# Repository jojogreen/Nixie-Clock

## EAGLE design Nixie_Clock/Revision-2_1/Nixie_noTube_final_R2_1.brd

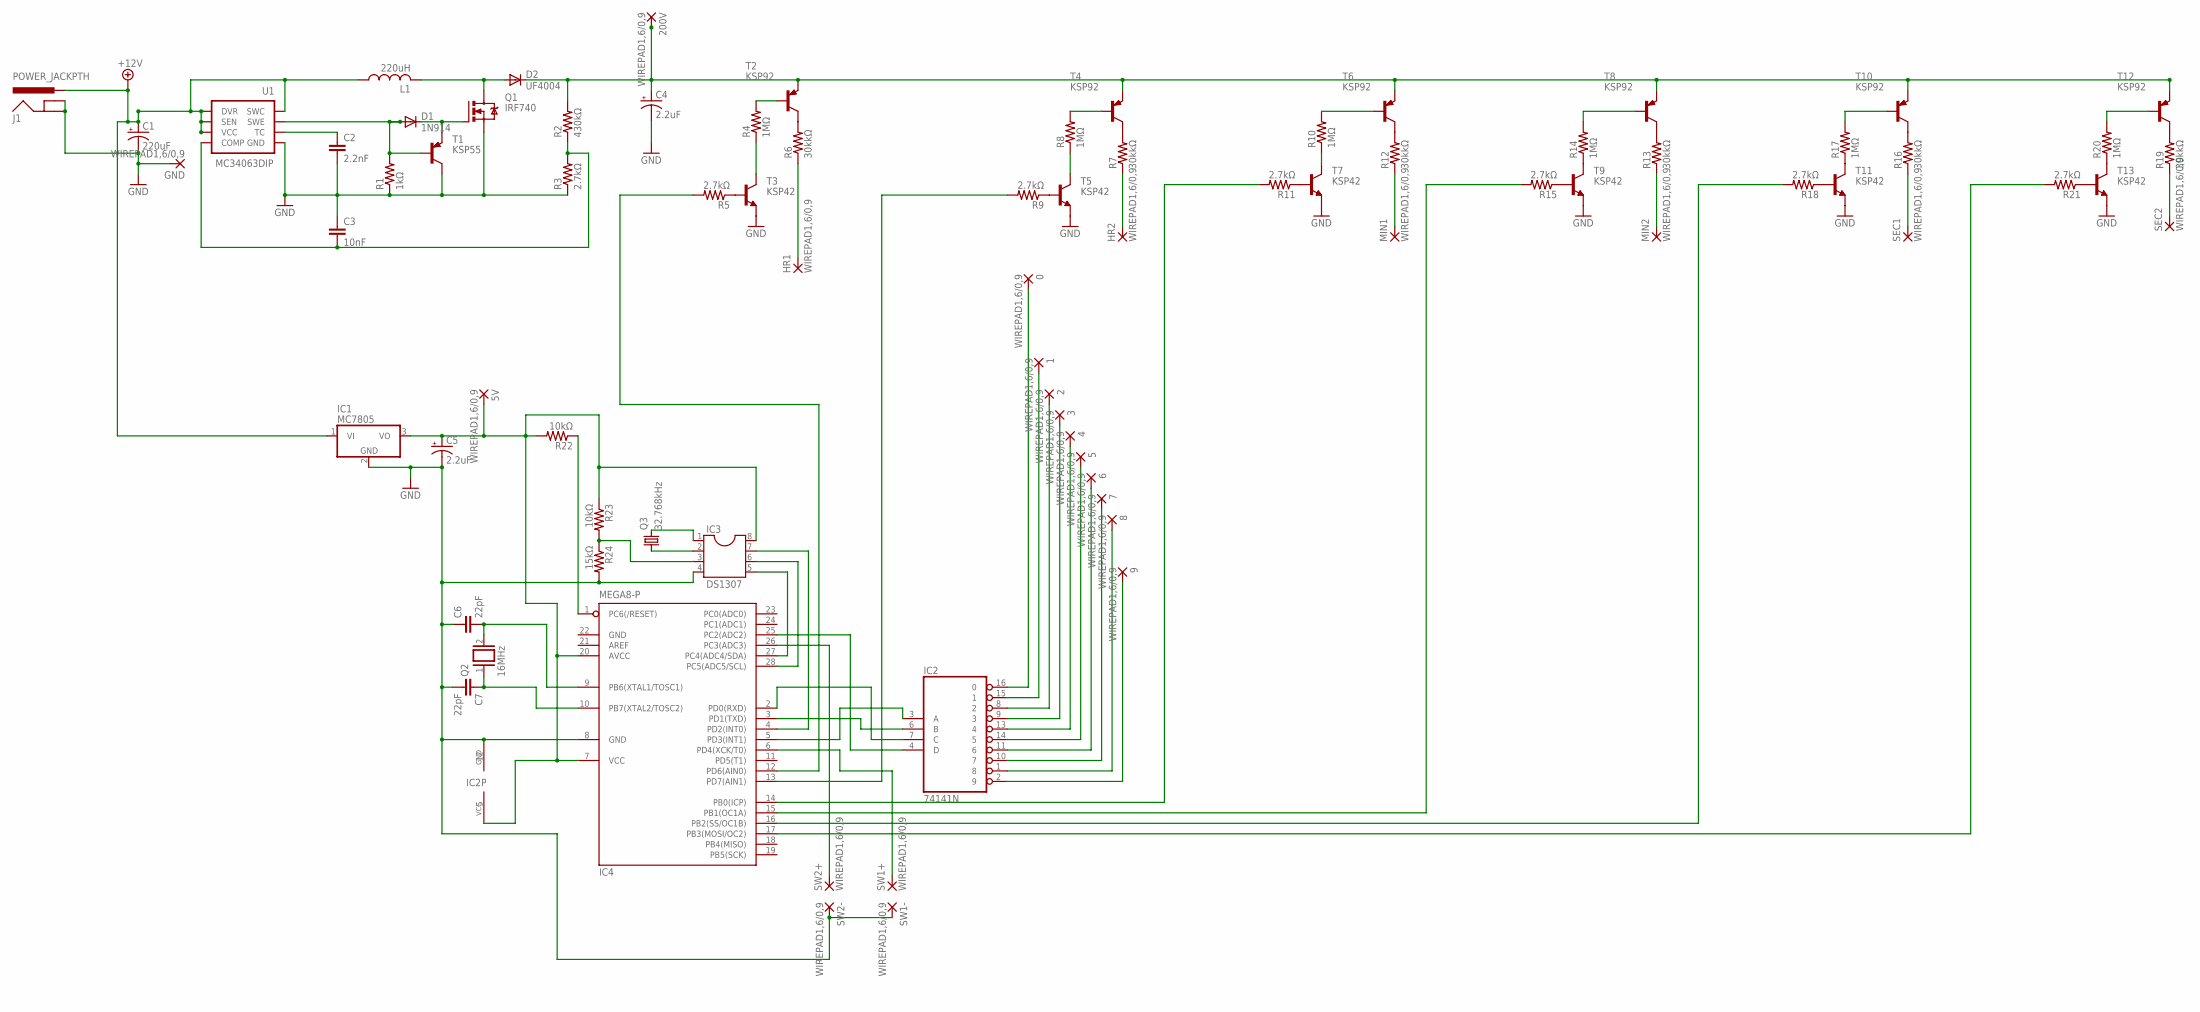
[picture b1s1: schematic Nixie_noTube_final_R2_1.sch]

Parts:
0, 1, 2, 3, 4, 5, 5V, 6, 7, 8, 9, 200V: WIREPAD1,6/0,9; 1,6/0,9
C1: 220uF; E5-10,5
C2: 2.2nF; CAP-PTH-SMALLEZ
C3: 10nF; CAP-PTH-SMALLEZ
C4, C5: 2.2uF; CPOL-RADIAL-100UF-25V
C6, C7: 22pF; C2.5-3
D1: 1N914; DO41-10
D2: UF4004; DO41-10
GND: WIREPAD1,6/0,9; 1,6/0,9
HR1, HR2: WIREPAD1,6/0,9; 1,6/0,9
IC1: MC7805; TO220V
IC2: 74141N; DIL16
IC3: DS1307; DIL08
IC4: MEGA8-P; DIL28-3
J1: POWER_JACKPTH; POWER_JACK_PTH
L1: 220uH; 6000-XXXX-RC
MIN1, MIN2: WIREPAD1,6/0,9; 1,6/0,9
Q1: IRF740; TO220BV
Q2: 16MHz; QS
Q3: 32.768kHz; TC26H
R1: 1kΩ; 0204/7
R2: 430kΩ; 0204/7
R3, R5, R9, R11, R15, R18, R21: 2.7kΩ; 0204/7
R4, R8, R10, R14, R17, R20: 1MΩ; 0204/7
R6, R7, R12, R13, R16, R19: 30kkΩ; 0204/7
R22, R23: 10kΩ; 0204/7
R24: 15kΩ; 0204/7
SEC1, SEC2: WIREPAD1,6/0,9; 1,6/0,9
SW1+, SW1-, SW2+, SW2-: WIREPAD1,6/0,9; 1,6/0,9
T1: KSP55; TO92-EBC
T2, T4, T6, T8, T10, T12: KSP92; TO92-EBC
T3, T5, T7, T9, T11, T13: KSP42; TO92-EBC
U1: MC34063DIP; DIP-08

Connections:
3V: IC3.3, R23.2, R24.1
5V: 5V.1, C5.1 (+), IC1.3 (VO), IC2.5 (VCC), IC3.8, IC4.7 (VCC), IC4.20 (AVCC), R22.2, R23.1
200V: 200V.1, C4.1 (+), D2.C, R2.2, T2.E, T4.E, T6.E, T8.E, T10.E, T12.E
+12V: C1.+, IC1.1 (VI), J1.PWR, L1.1, U1.1 (SWC), U1.6 (VCC), U1.7 (SEN), U1.8 (DVR)
GND: C1.-, C2.2, C3.1, C4.2 (-), C5.2 (-), C6.1, C7.2, GND.1, IC1.2 (GND), IC2.12 (GND), IC3.4, IC4.8 (GND), IC4.22 (GND), J1.GND, J1.GNDBREAK, Q1.S, R1.1, R3.1, R24.2, SW1-.1, SW2-.1, T1.C, T3.E, T5.E, T7.E, T9.E, T11.E, T13.E, U1.4 (GND)
H1: HR2.1, R7.1
unnamed: C2.1, U1.3 (TC)
unnamed: C3.2, R2.1, R3.2, U1.5 (COMP)
unnamed: D1.A, R1.2, T1.B, U1.2 (SWE)
unnamed: D1.C, Q1.G, T1.E
unnamed: D2.A, L1.2, Q1.D
unnamed: R19.1, SEC2.1
unnamed: R11.1, T7.B
unnamed: R6.2, T2.C
unnamed: R4.2, T2.B
unnamed: R4.1, T3.C
unnamed: R5.1, T3.B
unnamed: HR1.1, R6.1
unnamed: R7.2, T4.C
unnamed: R9.1, T5.B
unnamed: R8.2, T4.B
unnamed: R8.1, T5.C
unnamed: IC3.1, Q3.2
unnamed: R12.2, T6.C
unnamed: R10.1, T7.C
unnamed: MIN1.1, R12.1
unnamed: R10.2, T6.B
unnamed: R13.2, T8.C
unnamed: R14.1, T9.C
unnamed: R15.1, T9.B
unnamed: R14.2, T8.B
unnamed: MIN2.1, R13.1
unnamed: R16.2, T10.C
unnamed: R17.1, T11.C
unnamed: R18.1, T11.B
unnamed: R17.2, T10.B
unnamed: R16.1, SEC1.1
unnamed: R19.2, T12.C
unnamed: R20.1, T13.C
unnamed: R21.1, T13.B
unnamed: R20.2, T12.B
unnamed: IC3.2, Q3.1
unnamed: IC4.1 (PC6(/RESET)), R22.1
unnamed: IC2.6 (B), IC4.3 (PD1(TXD))
unnamed: C6.2, IC4.9 (PB6(XTAL1/TOSC1)), Q2.2
unnamed: C7.1, IC4.10 (PB7(XTAL2/TOSC2)), Q2.1
unnamed: IC2.7 (C), IC4.2 (PD0(RXD))
unnamed: IC2.4 (D), IC4.25 (PC2(ADC2))
unnamed: IC2.3 (A), IC4.5 (PD3(INT1))
unnamed: 0.1, IC2.16 (0)
unnamed: 1.1, IC2.15 (1)
unnamed: 2.1, IC2.8 (2)
unnamed: 3.1, IC2.9 (3)
unnamed: 4.1, IC2.13 (4)
unnamed: 5.1, IC2.14 (5)
unnamed: 6.1, IC2.11 (6)
unnamed: 7.1, IC2.10 (7)
unnamed: 8.1, IC2.1 (8)
unnamed: 9.1, IC2.2 (9)
unnamed: IC4.6 (PD4(XCK/T0)), SW1+.1
unnamed: IC4.26 (PC3(ADC3)), SW2+.1
unnamed: IC4.12 (PD6(AIN0)), R5.2
unnamed: IC4.13 (PD7(AIN1)), R9.2
unnamed: IC4.14 (PB0(ICP)), R11.2
unnamed: IC4.15 (PB1(OC1A)), R15.2
unnamed: IC4.16 (PB2(SS/OC1B)), R18.2
unnamed: IC4.17 (PB3(MOSI/OC2)), R21.2
SCL: IC3.6, IC4.28 (PC5(ADC5/SCL))
SDA: IC3.5, IC4.27 (PC4(ADC4/SDA))
SQWOUT: IC3.7, IC4.4 (PD2(INT0))

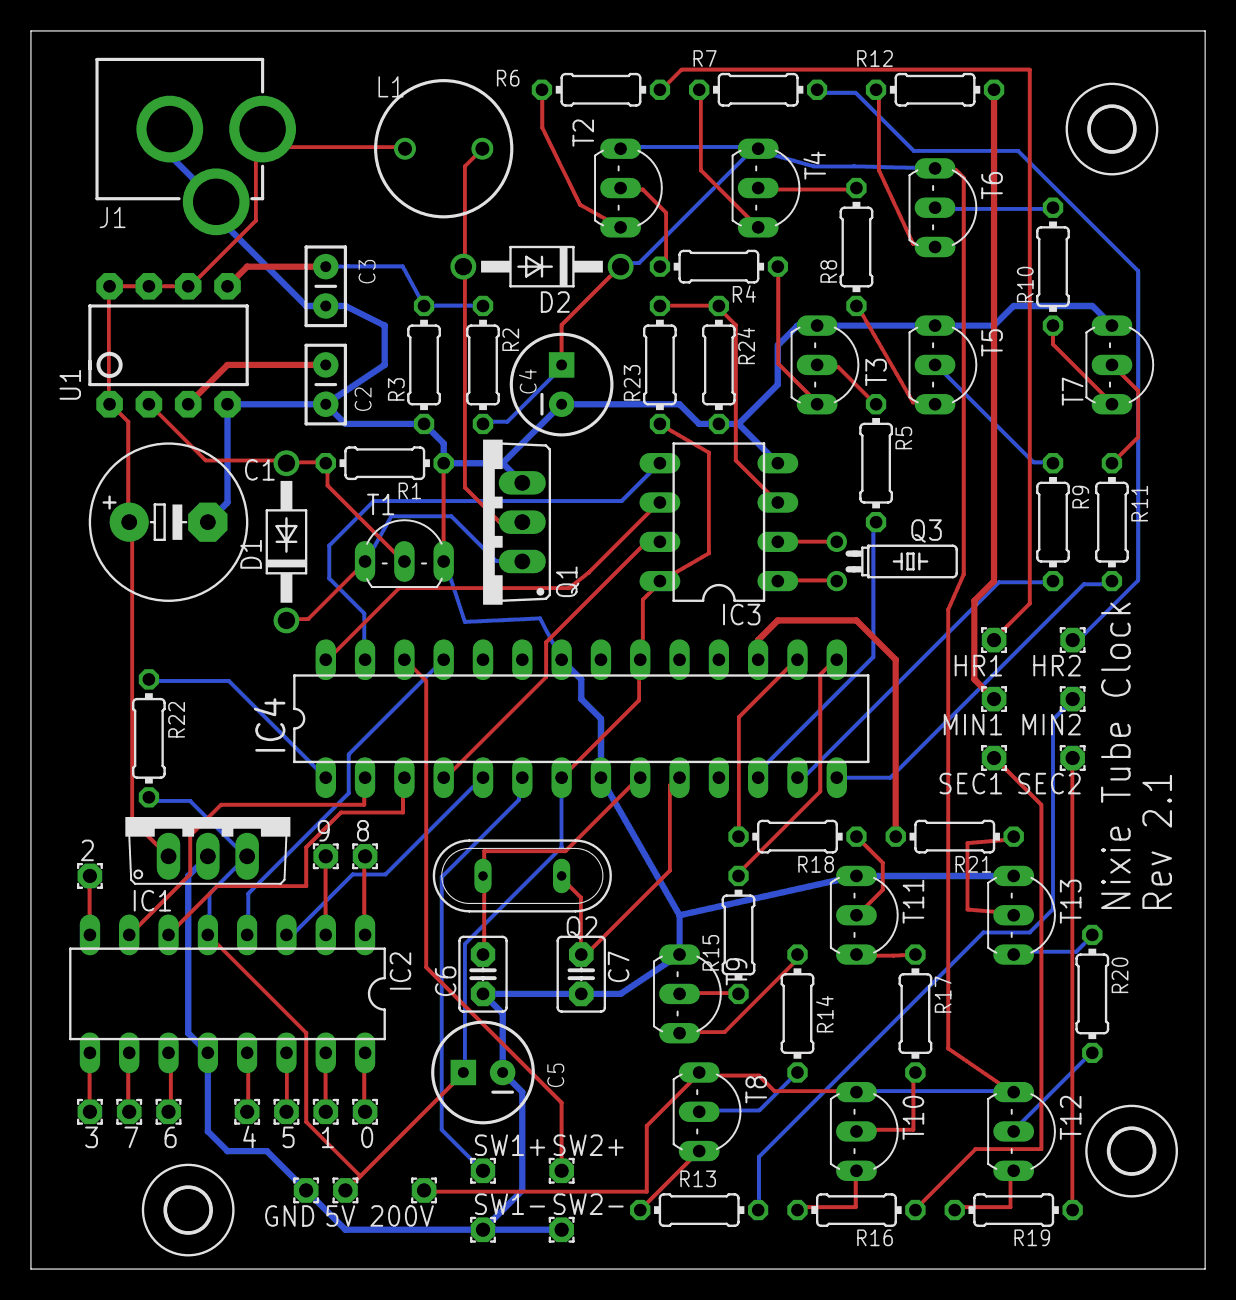
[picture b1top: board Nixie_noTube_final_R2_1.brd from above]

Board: 2 copper layers, 75.9 x 80.0 mm, 82 parts (0 on the bottom side), 70 nets.

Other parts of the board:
U$1, U$2, U$3: 2,8

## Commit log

2015-11-03 Added code base .ino for clock
2017-08-13 nixie tube files and arduino

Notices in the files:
parts and their libraries:
SparkFun-Capacitors: Licensing: Creative Commons ShareAlike 4.0 International - https://creativecommons.org/licenses/by-sa/4.0
